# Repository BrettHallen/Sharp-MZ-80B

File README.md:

# Sharp MZ-80B
My little repository of information about Sharp's MZ-80B all-in-one business computer from 1981.<br>

The MZ-80B is an evolution of the MZ-80K.<br>

WORK IN PROGRESS.<br>

NOTE! Any PCB designs are untested unless stated otherwise.  I have done my best to recreate them based on the schematics in the Service Manual.  (15/Feb/2026)<br>

## Videos
- [Part 1: Initial look & disassembly](https://youtu.be/cHQdRs1u79s)
- [Part 2: Keyboard refurbishment starts](https://youtu.be/vS2Di7rVlAI)
- [Part 3: Power Supply](/https://youtu.be/JZkt_DzX6Ko)
- [Part 4: Monitor & Tape Deck](https://youtu.be/Ke3hOiWCVKM)

## Specs
- Z80 at 4MHz (LH0080A)
- Power: ±5V, +12V
- 32KB RAM, expandable to 64KB
- 2KB ROM (Initial Program Loader, IPL)
- 2KB Character Generator ROM
- 2KB Character RAM
- 8KB Graphics RAM, expandable to 16KB (MZ-80GMK)

## [Components](/Components)
- IC2: Sharp X0240PA (Gate Array 14297)
- IC3: Sharp LH0080A (Z80 CPU)
- IC8: Sharp IX0285PA (IPL Boot ROM, 334-5700)
- IC19: 8253 PIT (Progammable Interval Timer)
- IC23: NEC D8255AC-5 PPI (Programmable Peripheral Interface)
- IC24: Sharp LH0081A (Z80 PIO)
- IC41: Toshiba TMM2016P-1 (2KB S-RAM)
- IC42: Sharp X0241PA (Gate Array 14298)
- IC43: Sharp X0242PA (Gate Array 14299)
- IC44: Sharp IX0286PA (CG-ROM, 334P-5701)
- DRAM: Sharp LH4116-3 (16k x 1-bit)

## [Manuals](/Manuals)
- MZ-80B Service Manual
- MZ-80B Owners Manual

## [ROMs](/ROMs)
- 2KB Initial Program Loader (IPL)
- 2KB Character Generator

## [32KB RAM Expansion](/Sharp_MZ-80B_RAM_III_IV_Expansion)
Internal expansion board to increase the RAM from 32KB to 64KB.  This design is from the Service Manual and so currently uses 4116 RAM chips.<br>

## [Base 8KB Graphics RAM (MZ-80GM)](/Sharp_MZ-80GM)
Reproduction of the base graphics RAM card (a.k.a. "GRAPHYICS-1") in the Sharp MZ-80B based on the service manual schematics.  I've updated it by replacing the original four 2KB 2016 SRAM chips with a single 32KB 62256.  Overkill, yes, but the 62256 is still available new - it reduces the chip count by four.<br>

## [8KB Graphics RAM Expansion (MZ-80GMK)](/Sharp_MZ-80GMK)
Expansion board (a.k.a. "GRAPHYICS-2") that connects to the internal Expansion Port (MZ-80EU) that doubles the graphics video RAM from 8KB to 16KB.  This design is from the Service Manual but uses a 32KB 62256 as these are still available new, rather than an obsolete 8KB 6264 or four 2KB 2016.<br>

## [DRAM to SRAM](/Sharp_MZ-80B_DRAM-to-SRAM)
Idea to replace the 16 x 4116 DRAMs of the original 32KB RAM plus the additional 16 x 4116 DRAMs of the expansion RAM with two 62256 SRAMs.<br>

## [Keyboard](/Keyboard)
Schematic and replacement PCB design.<br>

## [SD Card Interface](https://github.com/yanataka60/MZ-2000_SD)
Design (not mine!) to add SD card interface for the MZ-80B (and others).  It will work in an 80B with or without the Expansion Unit installed, which is neat.

## [Combo Graphics RAM + SD Interface](/Sharp_MZ-80GMSD)
As my MZ-80B doesn't have an expansion unit I thought about trying to add the 8KB Graphics RAM expansion (MZ-80GMK) aka "GRAPHYCS-2" on the same board as the SD interface above.  The SD board itself is still external, but the connection to the MZ-80B motherboard is included with the graphics RAM expansion.

## Power 
My 80B came from Japan so expects 100VAC and not the 240VAC we use in Australia.

### DC Requirements
| Voltage          | Current | Use                                |
|------------------|---------|------------------------------------|
| +5V regulated    | 2.5A    | motherboard & tape deck            |
| -5V regulated    | 10mA    | DRAM                               |
| +12V regulated   | 1.25A   | monitor & tape deck                |
| +12V unregulated |         | 9.5V-16.5V for tape deck solenoids |

### Connectors
Thanks to [Brad](https://www.youtube.com/@zbradbell) for figuring out they are TJC1-type.<br>

| Sharp ID      | TJC Type     | Use                                         |
|---------------|--------------|---------------------------------------------|
| QPLGN0303CEZZ | TJC1-3A      | 3-pin terminal for tape deck power on PSU   |
| DSOCN0083PAZZ | TJC1-3Y      | 3-pin socket & wires from tape deck to PSU  |
| QPLGN0103CEZZ | TJC1-1A      | 1-pin terminal for monitor power on PSU     |
| DSOCN0083PAZZ | TJC1-1Y      | 1-pin socket & wire from monitor to PSU     |
| DSOCN0098PAZZ | TJC1-4Y      | 4-pin socket & wire from PSU to motherboard |
| QPLGN0403CEZZ | TJC1-4A      | 4-pin terminal on motherboard               |
| QPLGN0303CEZZ | TJC1-3A      | 3-pin terminal for Expansion Unit power     |
|               | TJC1-T       | Contact type for sockets                    |

- [QPLGN0303CEZZ](/Images/Sharp_MZ-80B_QPLGN0303CEZZ_1.jpg)
- [DSOCN0098PAZZ](/Images/Sharp_MZ-80B_DSOCN0098PAZZ_1.png)

### New DC Power Supply
To solve my 240VAC-to-100VAC problem I thought about using a DC power supply input and then lazily using modern DC-DC switching regulators.  The main issue I can see is that the original design uses an unregulated +12VDC to power the tape eject solenoid.  This is picked up from the rectified transformer output before the +12VDC regulator which powers the monitor & tape.<br>

The tape solenoid expects a voltage between 9.5V and 16.5V.<br>

My idea was to, ahem, simply use a +15VDC input for the solenoid, and then use separate +5V, -5V and +12V regulators for the regulated supplies.  I've added some capacitors to try to soak up any voltage spikes generated by the solenoid action.<br>

Some notes:
- If I can replace the DRAM with SRAM, there is no longer a need for the -5V rail
- If I don't physically use the tape deck then there is no need for the +15V, i.e. "unregulated +12V"

## [External Audio/Video Output](/Sharp_MZ-CVBS)
A re-design of an [existing design](https://github.com/gamo256/MZ_CVBS) for replacing the CRT with an LCD, I think.  The original design uses obsolete parts (well, hard to get in Australia) so I've tried to re-design.  Let's see if it works ...<br>

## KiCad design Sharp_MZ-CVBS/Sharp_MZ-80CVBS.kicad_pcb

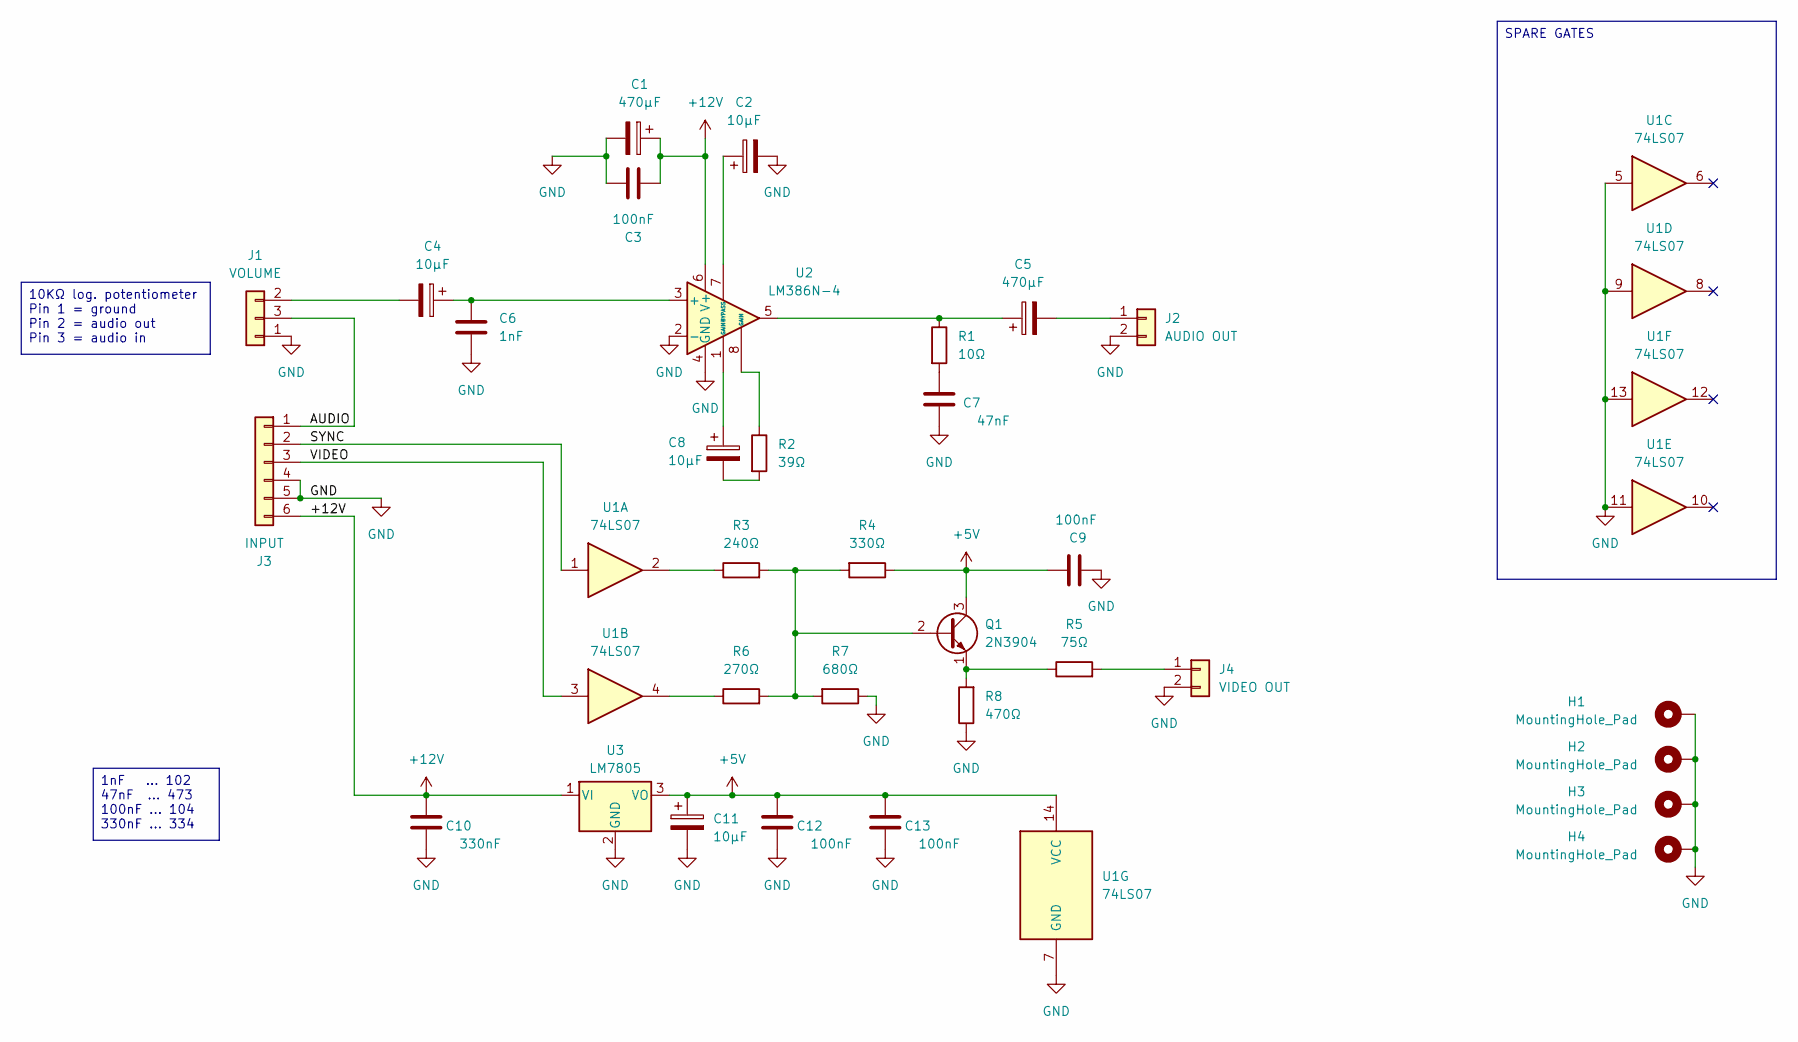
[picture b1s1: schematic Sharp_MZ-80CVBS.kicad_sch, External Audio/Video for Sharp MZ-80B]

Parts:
C1, C5: 470µF; CP_Radial_D10.0mm_P5.00mm
C2, C4, C8, C11: 10µF; CP_Radial_D5.0mm_P2.50mm
C3, C9, C12, C13: 100nF; C_Disc_D3.8mm_W2.6mm_P2.50mm
C6: 1nF; C_Disc_D3.8mm_W2.6mm_P2.50mm
C7: 47nF; C_Disc_D3.8mm_W2.6mm_P2.50mm
C10: 330nF; C_Disc_D3.8mm_W2.6mm_P2.50mm
H1, H2, H3, H4: MountingHole_Pad; MountingHole_3.2mm_M3_Pad
J1: VOLUME; PinHeader_1x03_P2.54mm_Vertical
J2: AUDIO OUT; PinHeader_1x02_P2.54mm_Vertical
J3: INPUT; PinHeader_1x06_P2.54mm_Vertical
J4: VIDEO OUT; PinHeader_1x02_P2.54mm_Vertical
Q1: 2N3904; TO-92_HandSolder
R1: 10Ω; R_Axial_DIN0207_L6.3mm_D2.5mm_P7.62mm_Horizontal
R2: 39Ω; R_Axial_DIN0207_L6.3mm_D2.5mm_P7.62mm_Horizontal
R3: 240Ω; R_Axial_DIN0207_L6.3mm_D2.5mm_P7.62mm_Horizontal
R4: 330Ω; R_Axial_DIN0207_L6.3mm_D2.5mm_P7.62mm_Horizontal
R5: 75Ω; R_Axial_DIN0207_L6.3mm_D2.5mm_P7.62mm_Horizontal
R6: 270Ω; R_Axial_DIN0207_L6.3mm_D2.5mm_P7.62mm_Horizontal
R7: 680Ω; R_Axial_DIN0207_L6.3mm_D2.5mm_P7.62mm_Horizontal
R8: 470Ω; R_Axial_DIN0207_L6.3mm_D2.5mm_P7.62mm_Horizontal
U1: 74LS07; DIP-14_W7.62mm
U2: LM386N-4; DIP-8_W7.62mm
U3: LM7805; TO-220-3_Horizontal_TabDown

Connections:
+5V: C9.1, C11.1, C12.1, C13.1, Q1.3 (C), R4.1, U1.14 (VCC), U3.3 (VO)
+12V: C1.1, C3.1, C10.1, J3.6, U2.6 (V+), U3.1 (VI)
/AUDIO: J1.3, J3.1
/SYNC: J3.2, U1.1
/VIDEO: J3.3, U1.3
GND: C1.2, C2.2, C3.2, C6.2, C7.2, C9.2, C10.2, C11.2, C12.2, C13.2, H1.1 (1_1), H2.1 (1_1), H3.1 (1_1), H4.1 (1_1), J1.1, J2.2, J3.4, J3.5, J4.2, R7.1, R8.1, U1.5, U1.7 (GND), U1.9, U1.11, U1.13, U2.2 (-), U2.4 (GND), U3.2 (GND)
unnamed: C5.1, R1.1, U2.5
unnamed: C7.1, R1.2
unnamed: C8.1, U2.1 (GAIN)
unnamed: C8.2, R2.2
unnamed: C4.2, J1.2
unnamed: C5.2, J2.1
unnamed: J4.1, R5.2
unnamed: Q1.2 (B), R3.2, R4.2, R6.2, R7.2
unnamed: Q1.1 (E), R5.1, R8.2
unnamed: R2.1, U2.8 (GAIN)
unnamed: R3.1, U1.2
unnamed: R6.1, U1.4
unnamed: C4.1, C6.1, U2.3 (+)
unnamed: C2.1, U2.7 (BYPASS)

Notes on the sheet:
1nF ... 102 47nF ... 473 100nF ... 104 330nF ... 334
SPARE GATES
10KΩ log. potentiometer Pin 1 = ground Pin 2 = audio out Pin 3 = audio in

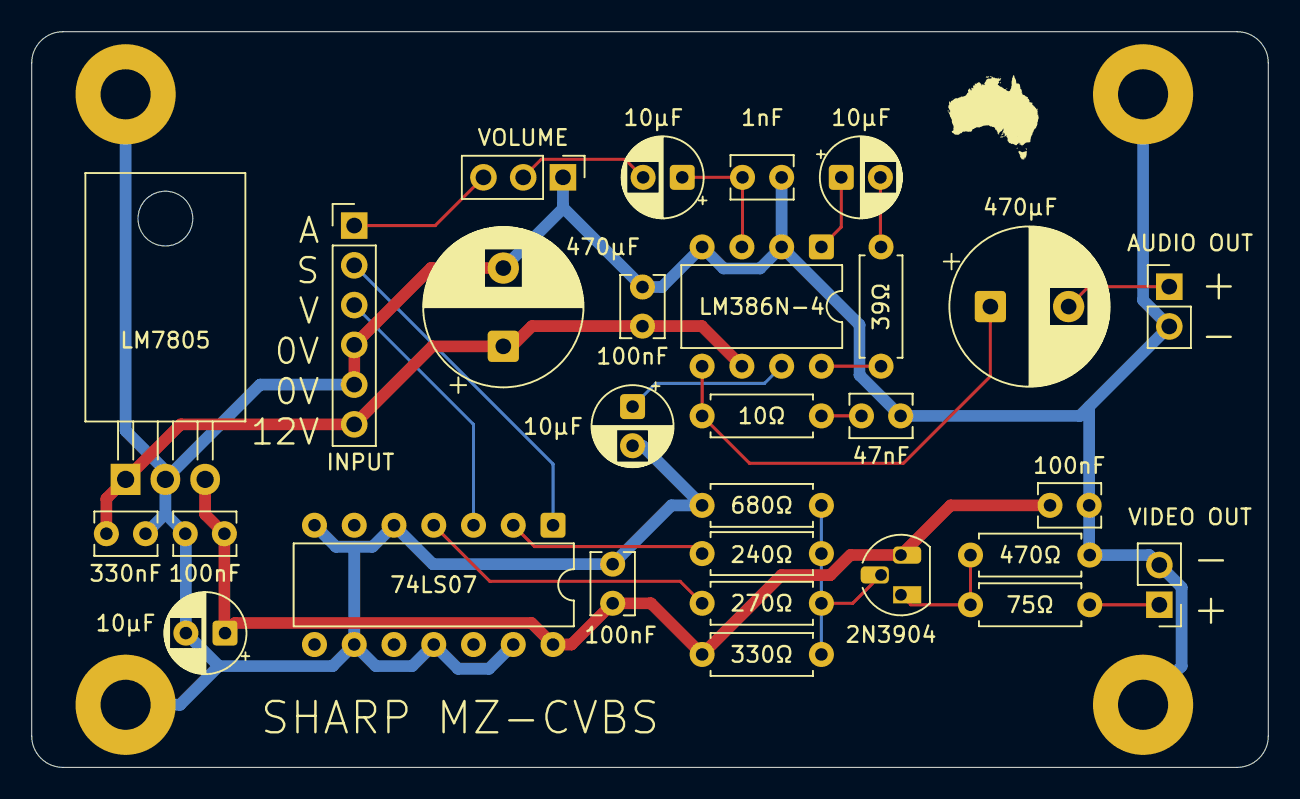
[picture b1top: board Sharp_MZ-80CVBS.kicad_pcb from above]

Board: 2 copper layers, 79.0 x 47.0 mm, 33 parts (0 on the bottom side), 20 nets.

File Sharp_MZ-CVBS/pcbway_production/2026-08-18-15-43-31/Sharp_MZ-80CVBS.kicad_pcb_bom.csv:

Designator,Quantity,Value,Footprint,Package,MPN,DNP,Mount_Type,Description,KiLib_Generator,Sim.Device,Sim.Pins
"C1, C5",2,470µF,CP_Radial_D10.0mm_P5.00mm,,,,tht,Polarized capacitor,capacitor/THT/other,,
C10,1,330nF,C_Disc_D3.8mm_W2.6mm_P2.50mm,,,,tht,Unpolarized capacitor,capacitor/THT/other,,
"C11, C2, C4, C8",4,10µF,CP_Radial_D5.0mm_P2.50mm,,,,tht,Polarized capacitor,capacitor/THT/other,,
"C12, C13, C3, C9",4,100nF,C_Disc_D3.8mm_W2.6mm_P2.50mm,,,,tht,Unpolarized capacitor,capacitor/THT/other,,
C6,1,1nF,C_Disc_D3.8mm_W2.6mm_P2.50mm,,,,tht,Unpolarized capacitor,capacitor/THT/other,,
C7,1,47nF,C_Disc_D3.8mm_W2.6mm_P2.50mm,,,,tht,Unpolarized capacitor,capacitor/THT/other,,
J1,1,VOLUME,PinHeader_1x03_P2.54mm_Vertical,,,,tht,"Generic connector, single row, 01x03, script generated (kicad-library-utils/schlib/autogen/connector/)",connector/pin_header_socket,,
J2,1,AUDIO OUT,PinHeader_1x02_P2.54mm_Vertical,,,,tht,"Generic connector, single row, 01x02, script generated (kicad-library-utils/schlib/autogen/connector/)",connector/pin_header_socket,,
J3,1,INPUT,PinHeader_1x06_P2.54mm_Vertical,,,,tht,"Generic connector, single row, 01x06, script generated (kicad-library-utils/schlib/autogen/connector/)",connector/pin_header_socket,,
J4,1,VIDEO OUT,PinHeader_1x02_P2.54mm_Vertical,,,,tht,"Generic connector, single row, 01x02, script generated (kicad-library-utils/schlib/autogen/connector/)",connector/pin_header_socket,,
Q1,1,2N3904,TO-92_HandSolder,,,,tht,"0.2A Ic, 40V Vce, Small Signal NPN Transistor, TO-92",,NPN,1=E 2=B 3=C
R1,1,10Ω,R_Axial_DIN0207_L6.3mm_D2.5mm_P7.62mm_Horizontal,,,,tht,Resistor,resistor/THT,,
R2,1,39Ω,R_Axial_DIN0207_L6.3mm_D2.5mm_P7.62mm_Horizontal,,,,tht,Resistor,resistor/THT,,
R3,1,240Ω,R_Axial_DIN0207_L6.3mm_D2.5mm_P7.62mm_Horizontal,,,,tht,Resistor,resistor/THT,,
R4,1,330Ω,R_Axial_DIN0207_L6.3mm_D2.5mm_P7.62mm_Horizontal,,,,tht,Resistor,resistor/THT,,
R5,1,75Ω,R_Axial_DIN0207_L6.3mm_D2.5mm_P7.62mm_Horizontal,,,,tht,Resistor,resistor/THT,,
R6,1,270Ω,R_Axial_DIN0207_L6.3mm_D2.5mm_P7.62mm_Horizontal,,,,tht,Resistor,resistor/THT,,
R7,1,680Ω,R_Axial_DIN0207_L6.3mm_D2.5mm_P7.62mm_Horizontal,,,,tht,Resistor,resistor/THT,,
R8,1,470Ω,R_Axial_DIN0207_L6.3mm_D2.5mm_P7.62mm_Horizontal,,,,tht,Resistor,resistor/THT,,
U1,1,74LS07,DIP-14_W7.62mm,,,,tht,Hex Buffers and Drivers With Open Collector High Voltage Outputs,package/DIP/legacy,,
U2,1,LM386N-4,DIP-8_W7.62mm,,,,tht,"Low Voltage Audio Power Amplifier, DIP-8/SOIC-8/SSOP-8",package/DIP/legacy,,
U3,1,LM7805,TO-220-3_Horizontal_TabDown,,,,tht,"Positive 1A 35V Linear Regulator, Fixed Output 5V, TO-220",package/TO_SOT/THT,,

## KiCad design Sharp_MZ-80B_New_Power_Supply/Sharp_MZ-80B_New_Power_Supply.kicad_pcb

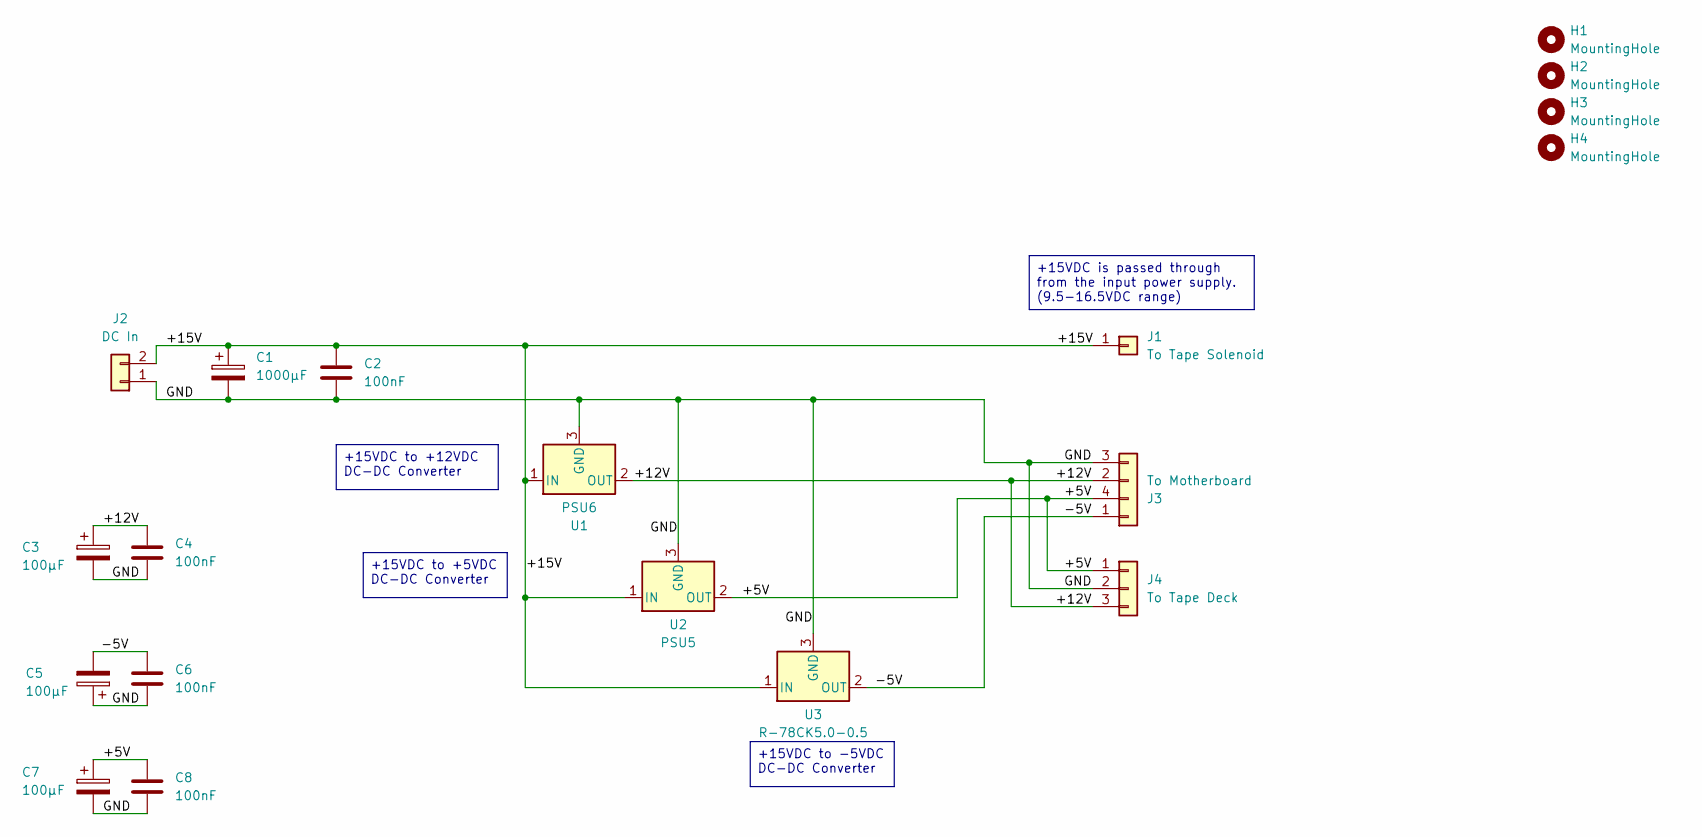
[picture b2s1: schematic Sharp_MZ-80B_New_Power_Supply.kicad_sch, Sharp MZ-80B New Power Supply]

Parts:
C1: 1000µF; CP_Radial_D16.0mm_P7.50mm
C2, C4, C6, C8: 100nF; C_Disc_D3.8mm_W2.6mm_P2.50mm
C3, C5, C7: 100µF; CP_Radial_D7.5mm_P2.50mm
H1, H2, H3, H4: MountingHole; MountingHole_3.2mm_M3
J1: To Tape Solenoid; TJC1-1A
J2: DC In; TJC1-2A
J3: To Motherboard; TJC1-4A
J4: To Tape Deck; TJC1-3A
U1: PSU6; TO-3
U2: PSU5; TO-3
U3: R-78CK5.0-0.5; TO-220-3_Vertical

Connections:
/+5V: C7.1, C8.1, J3.4, J4.1, U2.2 (OUT)
/+12V: C3.1, C4.1, J3.2, J4.3, U1.2 (OUT)
/+15V: C1.1, C2.1, J1.1, J2.2, U1.1 (IN), U2.1 (IN), U3.1 (IN)
/-5V: C5.2, C6.1, J3.1, U3.2 (OUT)
/GND: C1.2, C2.2, C3.2, C4.2, C5.1, C6.2, C7.2, C8.2, J2.1, J3.3, J4.2, U1.3 (GND), U2.3 (GND), U3.3 (GND)

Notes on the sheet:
+15VDC to +5VDC DC-DC Converter
+15VDC is passed through from the input power supply. (9.5-16.5VDC range)
+15VDC to +12VDC DC-DC Converter
+15VDC to -5VDC DC-DC Converter

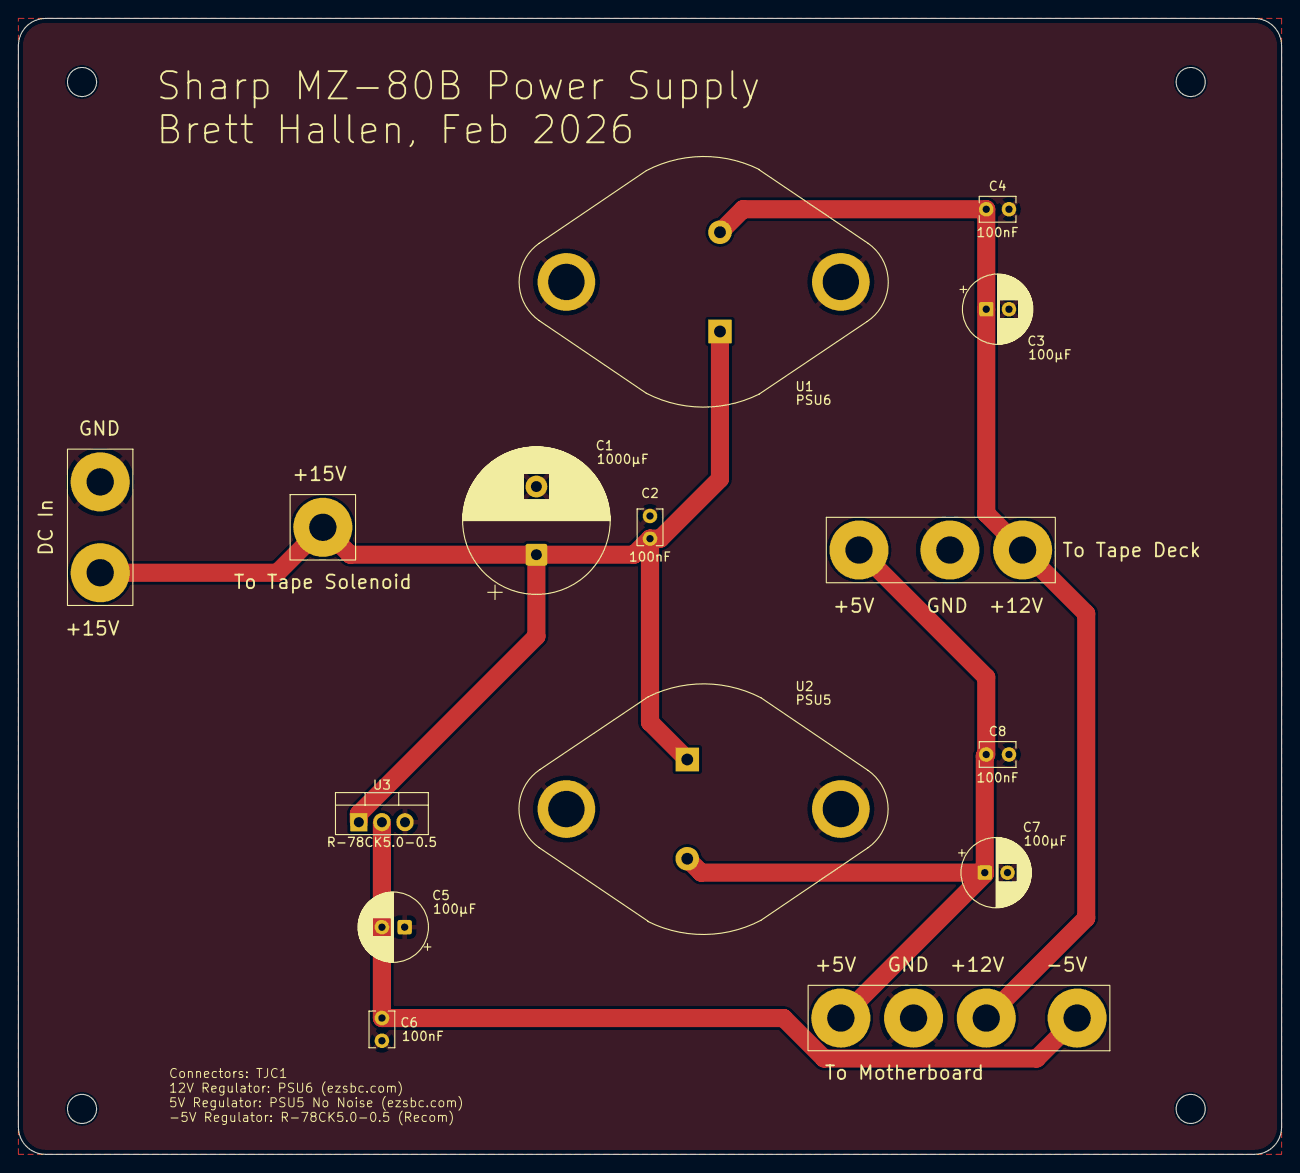
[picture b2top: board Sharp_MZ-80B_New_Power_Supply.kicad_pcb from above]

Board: 2 copper layers, 139.0 x 125.0 mm, 19 parts (0 on the bottom side), 5 nets.

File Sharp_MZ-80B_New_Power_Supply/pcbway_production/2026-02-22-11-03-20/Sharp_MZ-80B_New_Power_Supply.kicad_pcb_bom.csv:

Designator,Quantity,Value,Footprint,Package,MPN,DNP,Mount_Type,Description
C1,1,1000µF,CP_Radial_D16.0mm_P7.50mm,,,,tht,Polarized capacitor
"C2, C4, C6, C8",4,100nF,C_Disc_D3.8mm_W2.6mm_P2.50mm,,,,tht,Unpolarized capacitor
"C3, C5, C7",3,100µF,CP_Radial_D7.5mm_P2.50mm,,,,tht,Polarized capacitor
J1,1,To Tape Solenoid,TJC1-1A,,,,tht,"Generic connector, single row, 01x01, script generated (kicad-library-utils/schlib/autogen/connector/)"
J2,1,DC In,TJC1-2A,,,,tht,"Generic connector, single row, 01x02, script generated (kicad-library-utils/schlib/autogen/connector/)"
J3,1,To Motherboard,TJC1-4A,,,,tht,"Generic connector, single row, 01x04, script generated (kicad-library-utils/schlib/autogen/connector/)"
J4,1,To Tape Deck,TJC1-3A,,,,tht,"Generic connector, single row, 01x03, script generated (kicad-library-utils/schlib/autogen/connector/)"
U1,1,PSU6,TO-3,,,,tht,"Positive 1.5A 35V Linear Regulator, Fixed Output 5V, TO-220/TO-263/TO-252"
U2,1,PSU5,TO-3,,,,tht,"Positive 1.5A 35V Linear Regulator, Fixed Output 5V, TO-220/TO-263/TO-252"
U3,1,R-78CK5.0-0.5,TO-220-3_Vertical,,,,tht,"Positive 1.5A 35V Linear Regulator, Fixed Output 5V, TO-220/TO-263/TO-252"

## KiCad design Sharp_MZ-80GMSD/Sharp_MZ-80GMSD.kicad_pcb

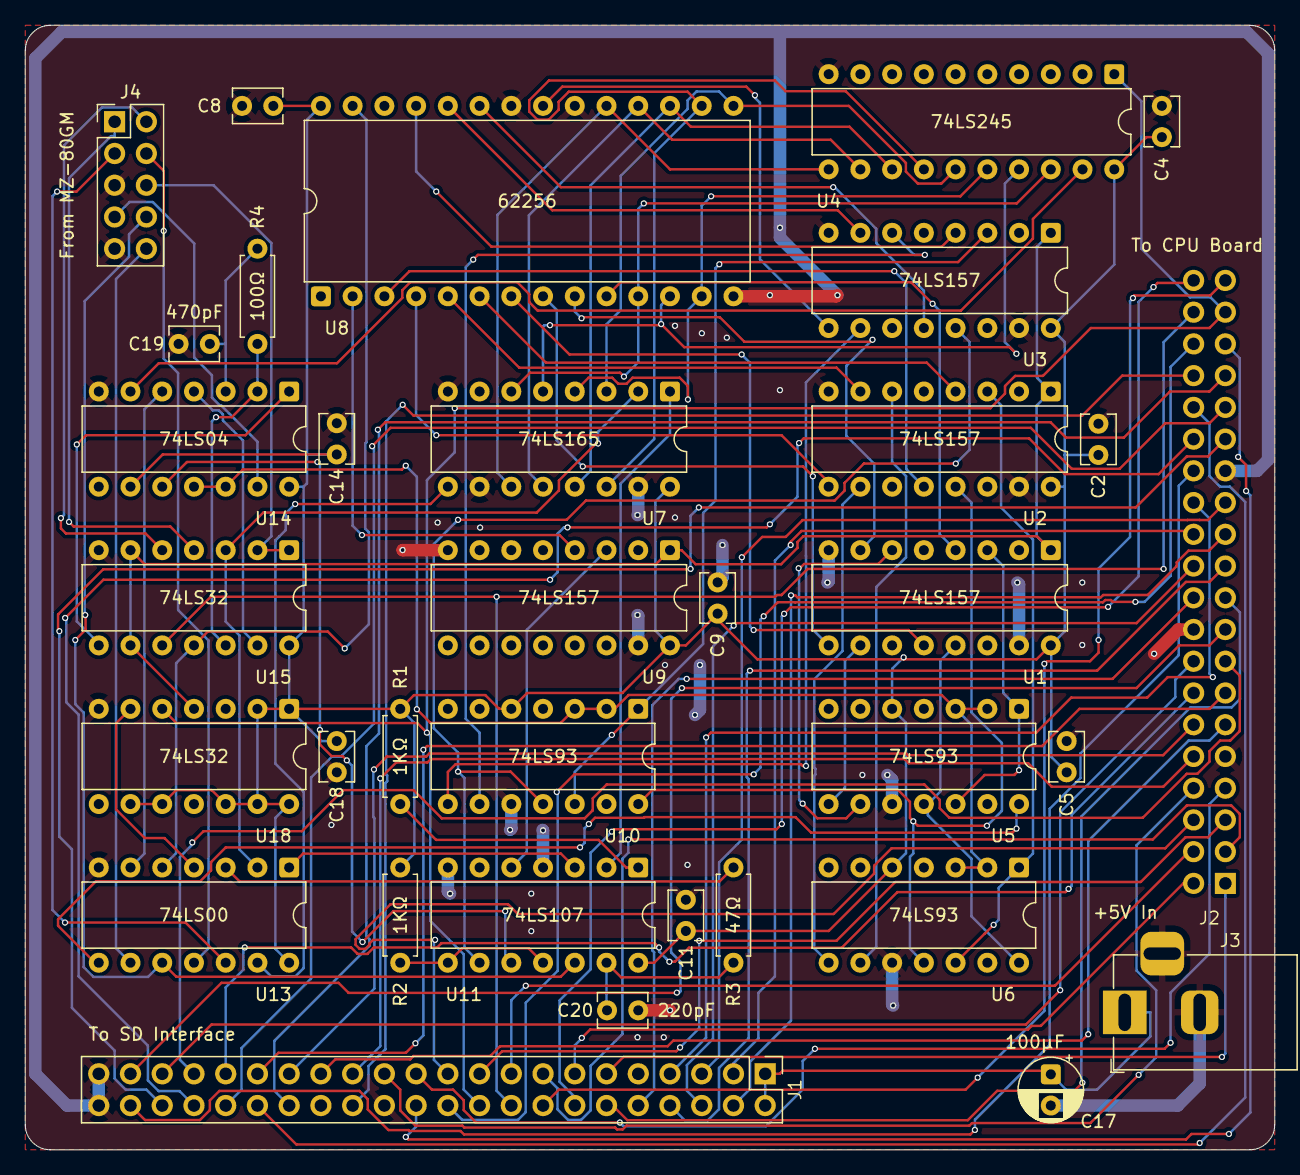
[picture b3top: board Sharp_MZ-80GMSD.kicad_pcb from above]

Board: 2 copper layers, 100.0 x 90.0 mm, 34 parts (1 on the bottom side), 102 nets.

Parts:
C2, C4, C5, C8, C9, C11, C14, C18: 100nF; C_Disc_D3.8mm_W2.6mm_P2.50mm
C17: 100µF; CP_Radial_D5.0mm_P2.50mm
C19: 470pF; C_Disc_D3.8mm_W2.6mm_P2.50mm
C20: 220pF; C_Disc_D3.8mm_W2.6mm_P2.50mm
J1: To SD Interface; PinHeader_2x22_P2.54mm_Vertical
J2: To CPU Board; PinSocket_2x20_P2.54mm_Vertical
J3: +5V In; BarrelJack_Horizontal
J4: From MZ-80GM; PinHeader_2x05_P2.54mm_Vertical
R1, R2: 1KΩ; R_Axial_DIN0207_L6.3mm_D2.5mm_P7.62mm_Horizontal
R3: 47Ω; R_Axial_DIN0207_L6.3mm_D2.5mm_P7.62mm_Horizontal
R4: 100Ω; R_Axial_DIN0207_L6.3mm_D2.5mm_P7.62mm_Horizontal
U1, U2, U3, U9: 74LS157; DIP-16_W7.62mm
U4: 74LS245; DIP-20_W7.62mm
U5, U6, U10: 74LS93; DIP-14_W7.62mm
U7: 74LS165; DIP-16_W7.62mm
U8: 62256; DIP-28_W15.24mm
U11: 74LS107; DIP-14_W7.62mm
U13: 74LS00; DIP-14_W7.62mm
U14: 74LS04; DIP-14_W7.62mm
U15, U18: 74LS32; DIP-14_W7.62mm

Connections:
+5V: C17.1, J1.A1 (Pin_a1), J1.B1 (Pin_b1), J3.1
/1M: J4.8, U11.12 (C), U13.10
/8M: J4.6, U15.1, U15.2
/A0: J1.A21 (Pin_a21), J2.17
/A1: J1.A20 (Pin_a20), J2.16
/A2: J1.A19 (Pin_a19), J2.15
/A3: J1.A18 (Pin_a18), J2.14
/A4: J1.A17 (Pin_a17), J2.13
/A5: J1.A16 (Pin_a16), J2.12
/A6: J1.A15 (Pin_a15), J2.11
/A7: J1.A14 (Pin_a14), J2.10
/A8: J1.A13 (Pin_a13), J2.8
/A9: J1.A12 (Pin_a12), J2.7
/A10: J1.A11 (Pin_a11), J2.6
/A11: J1.A10 (Pin_a10), J2.5
/A12: J1.A9 (Pin_a9), J2.4
/A13: J1.A8 (Pin_a8), J2.3
/A14: J1.A7 (Pin_a7), J2.2
/A15: J1.A6 (Pin_a6), J2.1
/BUS Φ: J1.B7 (Pin_b7), J2.40
/CLOCK: U7.2 (CP), U13.2, U15.3
/D0: J1.A4 (Pin_a4), J2.26
/D1: J1.A3 (Pin_a3), J2.25
/D2: J1.A2 (Pin_a2), J2.24
/D3: J1.B2 (Pin_b2), J2.23
/D4: J1.B3 (Pin_b3), J2.22
/D5: J1.B4 (Pin_b4), J2.21
/D6: J1.B5 (Pin_b5), J2.20
/D7: J1.B6 (Pin_b6), J2.19
/G0: J4.3, U13.12
/G1: J4.1, U15.4
/G_{0}: U1.3 (I1a), U5.1 (CP1..3), U5.12 (Q0)
/G_{1}: U1.6 (I1b), U5.9 (Q1)
/G_{2}: U1.10 (I1c), U5.8 (Q2)
/G_{3}: U1.13 (I1d), U5.11 (Q3), U6.14 (CP0)
/G_{4}: U2.3 (I1a), U6.1 (CP1..3), U6.12 (Q0)
/G_{5}: U2.6 (I1b), U6.9 (Q1)
/G_{6}: U2.10 (I1c), U6.8 (Q2)
/G_{7}: U2.13 (I1d), U6.11 (Q3), U10.14 (CP0)
/G_{8}: U3.3 (I1a), U10.1 (CP1..3), U10.12 (Q0)
/G_{9}: U3.6 (I1b), U10.9 (Q1)
/G_{10}: U3.10 (I1c), U10.8 (Q2)
/G_{11}: U3.13 (I1d), U10.11 (Q3), U11.9 (C)
/G_{12}: U9.3 (I1a), U11.5 (Q)
/IE0: J1.B16 (Pin_b16), J2.33
/RA_{0}: U1.4 (Za), U8.10 (A0)
/RA_{1}: U1.7 (Zb), U8.9 (A1)
/RA_{2}: U1.9 (Zc), U8.8 (A2)
/RA_{3}: U1.12 (Zd), U8.7 (A3)
/RA_{4}: U2.4 (Za), U8.6 (A4)
/RA_{5}: U2.7 (Zb), U8.5 (A5)
/RA_{6}: U2.9 (Zc), U8.4 (A6)
/RA_{7}: U2.12 (Zd), U8.3 (A7)
/RA_{8}: U3.4 (Za), U8.25 (A8)
/RA_{9}: U3.7 (Zb), U8.24 (A9)
/RA_{10}: U3.9 (Zc), U8.21 (A10)
/RA_{11}: U3.12 (Zd), U8.23 (A11)
/RA_{12}: U8.2 (A12), U9.4 (Za)
/RD_{0}: U4.18 (B0), U7.6 (D7), U8.11 (Q0)
/RD_{1}: U4.17 (B1), U7.5 (D6), U8.12 (Q1)
/RD_{2}: U4.16 (B2), U7.4 (D5), U8.13 (Q2)
/RD_{3}: U4.15 (B3), U7.3 (D4), U8.15 (Q3)
/RD_{4}: U4.14 (B4), U7.14 (D3), U8.16 (Q4)
/RD_{5}: U4.13 (B5), U7.13 (D2), U8.17 (Q5)
/RD_{6}: U4.12 (B6), U7.12 (D1), U8.18 (Q6)
/RD_{7}: U4.11 (B7), U7.11 (D0), U8.19 (Q7)
/RESET: J1.B17 (Pin_b17), J2.32
/SELECT: U1.1 (S), U2.1 (S), U3.1 (S), U9.1 (S), U15.6, U15.9, U18.4
/SHIFT/~LOAD: U7.1 (~PL), U11.2 (~Q)
/~C SED: J4.2, U15.5
/~EX INT: J1.B19 (Pin_b19), J2.30
/~EX RESET: J1.B18 (Pin_b18), J2.31
/~EX WAIT: J1.B20 (Pin_b20), J2.29
/~G OUT 2: J4.4, U13.11
/~HALT: J1.B14 (Pin_b14), J2.34
/~HBLK: J4.10, U13.9
/~IOREQ: J1.B11 (Pin_b11), J2.36
/~M1: J1.B8 (Pin_b8), J2.39
/~MNI: J1.B21 (Pin_b21), J2.28
/~MREQ: J1.B12 (Pin_b12), J2.35
/~RD: J1.B10 (Pin_b10), J2.37, U4.1 (A->B), U18.5
/~VBLK: J4.7, U14.13
/~WE: U8.27 (~WE), U13.5, U15.11
/~WR: J1.B9 (Pin_b9), J2.38, U15.10
GND: C2.2, C4.2, C5.2, C8.2, C9.1, C11.1, C14.1, C17.2, C18.1, C19.1, C20.2, J1.A5 (Pin_a5), J1.A22 (Pin_a22), J1.B13 (Pin_b13), J1.B22 (Pin_b22), J2.9, J2.18, J2.27, J3.2, J4.5, J4.9, U1.8 (GND), U1.15 (E), U2.8 (GND), U2.15 (E), U3.8 (GND), U3.15 (E), U4.10 (GND), U5.10 (GND), U6.10 (GND), U7.8 (GND), U7.10 (DS), U7.15 (~CE), U8.14 (GND), U8.20 (~CS), U8.22 (~OE), U9.8 (GND), U9.15 (E), U10.10 (GND), U11.4 (K), U11.7 (GND), U13.7 (GND), U14.7 (GND), U15.7 (GND), U18.7 (GND)
unnamed: C19.2, R4.2, U14.3
unnamed: R3.2, U13.3
unnamed: R4.1, U14.2, U15.12
unnamed: U4.19 (CE), U14.6
unnamed: U5.14 (CP0), U13.8
unnamed: U7.9 (Q7), U13.13
unnamed: U5.2 (R0(1)), U5.3 (R0(2)), U6.2 (R0(1)), U6.3 (R0(2)), U10.2 (R0(1)), U10.3 (R0(2)), U14.11, U14.12
unnamed: R1.2, U11.1 (J)
unnamed: U11.3 (Q), U13.1
unnamed: C20.1, R3.1, U11.13 (~R)
unnamed: R2.2, U11.8 (J), U11.11 (K)
unnamed: U11.10 (~R), U14.10
unnamed: U13.4, U18.6
unnamed: U13.6, U14.5
unnamed: U14.1, U15.8
unnamed: U14.4, U15.13
VCC: C2.1, C4.1, C5.1, C8.1, C9.2, C11.2, C14.2, C18.2, R1.1, R2.1, U1.16 (VCC), U2.16 (VCC), U3.16 (VCC), U4.20 (VCC), U5.5 (VCC), U6.5 (VCC), U7.16 (VCC), U8.28 (VCC), U9.16 (VCC), U10.5 (VCC), U11.14 (VCC), U13.14 (VCC), U14.9, U14.14 (VCC), U15.14 (VCC), U18.1, U18.2, U18.9, U18.10, U18.12, U18.13, U18.14 (VCC)

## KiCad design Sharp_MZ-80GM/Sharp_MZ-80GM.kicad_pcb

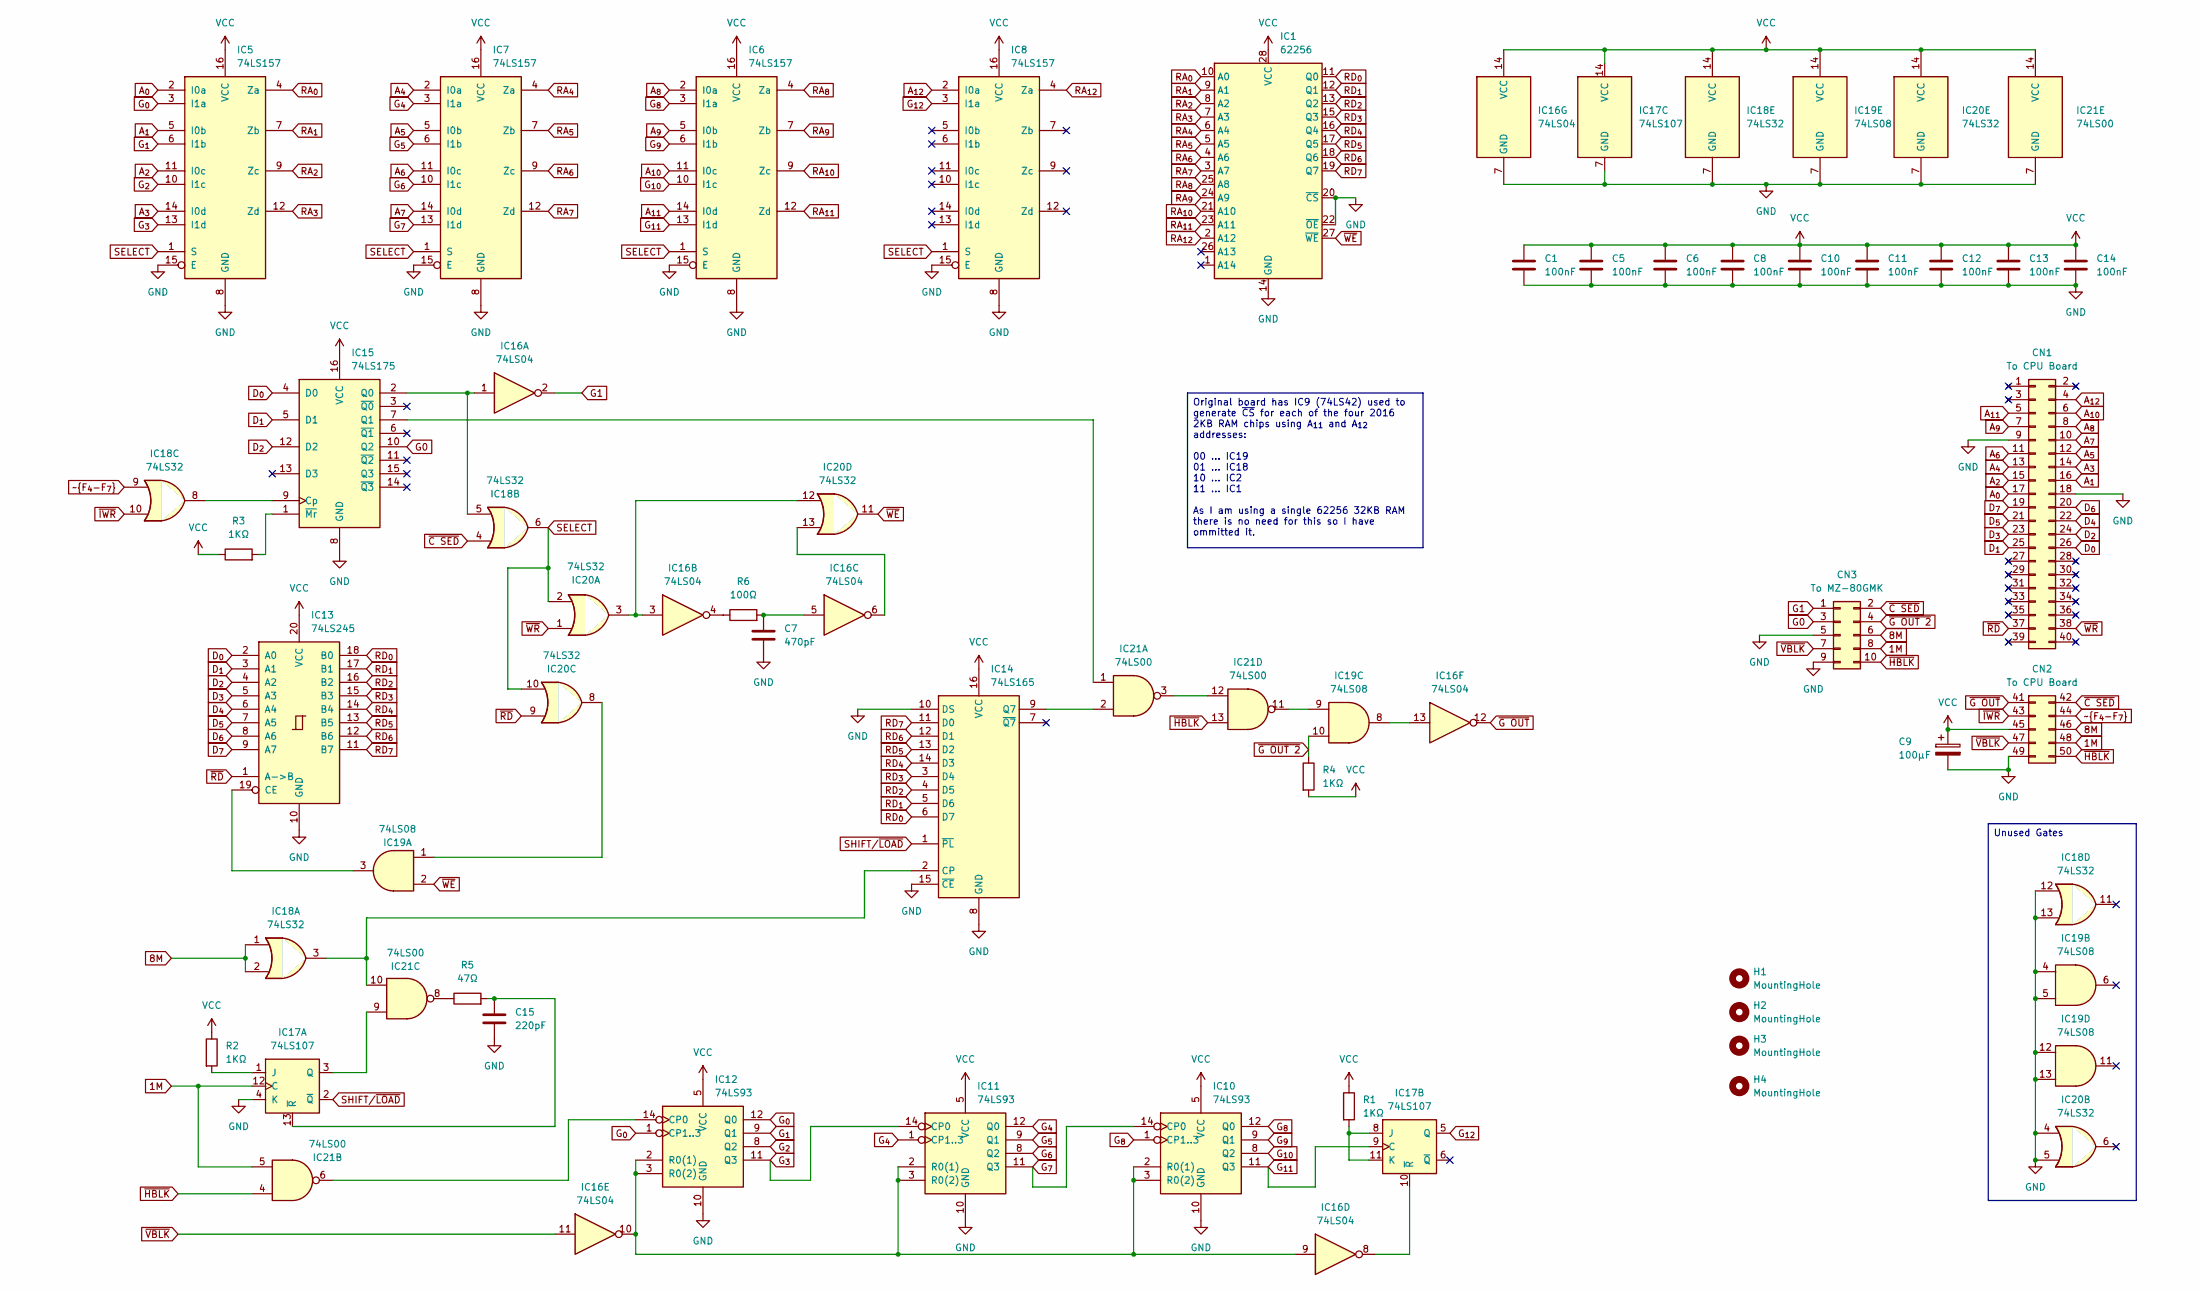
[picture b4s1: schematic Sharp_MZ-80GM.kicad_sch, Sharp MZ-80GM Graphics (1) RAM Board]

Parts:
C1, C5, C6, C8, C10, C11, C12, C13, C14: 100nF; C_Disc_D3.8mm_W2.6mm_P2.50mm
C7: 470pF; C_Disc_D3.8mm_W2.6mm_P2.50mm
C9: 100µF; CP_Radial_D5.0mm_P2.50mm
C15: 220pF; C_Disc_D3.8mm_W2.6mm_P2.50mm
CN1: To CPU Board; PinHeader_2x20_P2.54mm_Vertical
CN2: To CPU Board; PinHeader_2x05_P2.54mm_Vertical
CN3: To MZ-80GMK; PinHeader_2x05_P2.54mm_Horizontal
H1, H2, H3, H4: MountingHole; MountingHole_5.3mm_M5
IC1: 62256; DIP-28_W15.24mm
IC5, IC6, IC7, IC8: 74LS157; DIP-16_W7.62mm
IC10, IC11, IC12: 74LS93; DIP-14_W7.62mm
IC13: 74LS245; DIP-20_W7.62mm
IC14: 74LS165; DIP-16_W7.62mm
IC15: 74LS175; DIP-16_W7.62mm
IC16: 74LS04; DIP-14_W7.62mm
IC17: 74LS107; DIP-14_W7.62mm
IC18, IC20: 74LS32; DIP-14_W7.62mm
IC19: 74LS08; DIP-14_W7.62mm
IC21: 74LS00; DIP-14_W7.62mm
R1, R2, R3, R4: 1KΩ; R_Axial_DIN0207_L6.3mm_D2.5mm_P7.62mm_Horizontal
R5: 47Ω; R_Axial_DIN0207_L6.3mm_D2.5mm_P7.62mm_Horizontal
R6: 100Ω; R_Axial_DIN0207_L6.3mm_D2.5mm_P7.62mm_Horizontal

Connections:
1M: CN2.48 (Pin_8), CN3.8, IC17.12 (C), IC21.5
8M: CN2.46 (Pin_6), CN3.6, IC18.1, IC18.2
A_{0}: CN1.17 (A0), IC5.2 (I0a)
A_{1}: CN1.16 (A1), IC5.5 (I0b)
A_{2}: CN1.15 (A2), IC5.11 (I0c)
A_{3}: CN1.14 (A3), IC5.14 (I0d)
A_{4}: CN1.13 (A4), IC7.2 (I0a)
A_{5}: CN1.12 (A5), IC7.5 (I0b)
A_{6}: CN1.11 (A6), IC7.11 (I0c)
A_{7}: CN1.10 (A7), IC7.14 (I0d)
A_{8}: CN1.8 (A8), IC6.2 (I0a)
A_{9}: CN1.7 (A9), IC6.5 (I0b)
A_{10}: CN1.6 (A10), IC6.11 (I0c)
A_{11}: CN1.5 (A11), IC6.14 (I0d)
A_{12}: CN1.4 (A12), IC8.2 (I0a)
D_{0}: CN1.26 (D0), IC13.2 (A0), IC15.4 (D0)
D_{1}: CN1.25 (D1), IC13.3 (A1), IC15.5 (D1)
D_{2}: CN1.24 (D2), IC13.4 (A2), IC15.12 (D2)
D_{3}: CN1.23 (D3), IC13.5 (A3)
D_{4}: CN1.22 (D4), IC13.6 (A4)
D_{5}: CN1.21 (D5), IC13.7 (A5)
D_{6}: CN1.20 (D6), IC13.8 (A6)
D_{7}: CN1.19 (D7), IC13.9 (A7)
G0: CN3.3, IC15.10 (Q2)
G1: CN3.1, IC16.2
GND: C1.2, C5.2, C6.2, C7.2, C8.2, C9.2, C10.2, C11.2, C12.2, C13.2, C14.2, C15.2, CN1.9 (GND), CN1.18 (GND), CN2.49 (GND), CN3.5, CN3.9, IC1.14 (GND), IC1.20 (~CS), IC1.22 (~OE), IC5.8 (GND), IC5.15 (E), IC6.8 (GND), IC6.15 (E), IC7.8 (GND), IC7.15 (E), IC8.8 (GND), IC8.15 (E), IC10.10 (GND), IC11.10 (GND), IC12.10 (GND), IC13.10 (GND), IC14.8 (GND), IC14.10 (DS), IC14.15 (~CE), IC15.8 (GND), IC16.7 (GND), IC17.4 (K), IC17.7 (GND), IC18.7 (GND), IC18.12, IC18.13, IC19.4, IC19.5, IC19.7 (GND), IC19.12, IC19.13, IC20.4, IC20.5, IC20.7 (GND), IC21.7 (GND)
G_{0}: IC5.3 (I1a), IC12.1 (CP1..3), IC12.12 (Q0)
G_{1}: IC5.6 (I1b), IC12.9 (Q1)
G_{2}: IC5.10 (I1c), IC12.8 (Q2)
G_{3}: IC5.13 (I1d), IC11.14 (CP0), IC12.11 (Q3)
G_{4}: IC7.3 (I1a), IC11.1 (CP1..3), IC11.12 (Q0)
G_{5}: IC7.6 (I1b), IC11.9 (Q1)
G_{6}: IC7.10 (I1c), IC11.8 (Q2)
G_{7}: IC7.13 (I1d), IC10.14 (CP0), IC11.11 (Q3)
G_{8}: IC6.3 (I1a), IC10.1 (CP1..3), IC10.12 (Q0)
G_{9}: IC6.6 (I1b), IC10.9 (Q1)
G_{10}: IC6.10 (I1c), IC10.8 (Q2)
G_{11}: IC6.13 (I1d), IC10.11 (Q3), IC17.9 (C)
G_{12}: IC8.3 (I1a), IC17.5 (Q)
unnamed: C7.1, IC16.5, R6.2
unnamed: IC10.2 (R0(1)), IC10.3 (R0(2)), IC11.2 (R0(1)), IC11.3 (R0(2)), IC12.2 (R0(1)), IC12.3 (R0(2)), IC16.9, IC16.10
unnamed: IC12.14 (CP0), IC21.6
unnamed: IC13.19 (CE), IC19.3
unnamed: IC14.2 (CP), IC18.3, IC21.10
unnamed: IC14.9 (Q7), IC21.2
unnamed: IC15.9 (Cp), IC18.8
unnamed: IC15.2 (Q0), IC16.1, IC18.5
unnamed: IC15.7 (Q1), IC21.1
unnamed: IC15.1 (~Mr), R3.2
unnamed: IC16.3, IC20.3, IC20.12
unnamed: IC16.4, R6.1
unnamed: IC16.6, IC20.13
unnamed: IC16.13, IC19.8
unnamed: IC17.1 (J), R2.2
unnamed: IC17.3 (Q), IC21.9
unnamed: C15.1, IC17.13 (~R), R5.2
unnamed: IC17.8 (J), IC17.11 (K), R1.2
unnamed: IC16.8, IC17.10 (~R)
unnamed: IC19.1, IC20.8
unnamed: IC19.9, IC21.11
unnamed: IC21.8, R5.1
unnamed: IC21.3, IC21.12
RA_{0}: IC1.10 (A0), IC5.4 (Za)
RA_{1}: IC1.9 (A1), IC5.7 (Zb)
RA_{2}: IC1.8 (A2), IC5.9 (Zc)
RA_{3}: IC1.7 (A3), IC5.12 (Zd)
RA_{4}: IC1.6 (A4), IC7.4 (Za)
RA_{5}: IC1.5 (A5), IC7.7 (Zb)
RA_{6}: IC1.4 (A6), IC7.9 (Zc)
RA_{7}: IC1.3 (A7), IC7.12 (Zd)
RA_{8}: IC1.25 (A8), IC6.4 (Za)
RA_{9}: IC1.24 (A9), IC6.7 (Zb)
RA_{10}: IC1.21 (A10), IC6.9 (Zc)
RA_{11}: IC1.23 (A11), IC6.12 (Zd)
RA_{12}: IC1.2 (A12), IC8.4 (Za)
RD_{0}: IC1.11 (Q0), IC13.18 (B0), IC14.6 (D7)
RD_{1}: IC1.12 (Q1), IC13.17 (B1), IC14.5 (D6)
RD_{2}: IC1.13 (Q2), IC13.16 (B2), IC14.4 (D5)
RD_{3}: IC1.15 (Q3), IC13.15 (B3), IC14.3 (D4)
RD_{4}: IC1.16 (Q4), IC13.14 (B4), IC14.14 (D3)
RD_{5}: IC1.17 (Q5), IC13.13 (B5), IC14.13 (D2)
RD_{6}: IC1.18 (Q6), IC13.12 (B6), IC14.12 (D1)
RD_{7}: IC1.19 (Q7), IC13.11 (B7), IC14.11 (D0)
SELECT: IC5.1 (S), IC6.1 (S), IC7.1 (S), IC8.1 (S), IC18.6, IC20.2, IC20.10
SHIFT/~LOAD: IC14.1 (~PL), IC17.2 (~Q)
VCC: C1.1, C5.1, C6.1, C8.1, C9.1, C10.1, C11.1, C12.1, C13.1, C14.1, CN2.45 (+5V), IC1.28 (VCC), IC5.16 (VCC), IC6.16 (VCC), IC7.16 (VCC), IC8.16 (VCC), IC10.5 (VCC), IC11.5 (VCC), IC12.5 (VCC), IC13.20 (VCC), IC14.16 (VCC), IC15.16 (VCC), IC16.14 (VCC), IC17.14 (VCC), IC18.14 (VCC), IC19.14 (VCC), IC20.14 (VCC), IC21.14 (VCC), R1.1, R2.1, R3.1, R4.2
~C SED: CN2.42 (Pin_2), CN3.2, IC18.4
~F_{4-F_{7}}: CN2.44 (Pin_4), IC18.9
~G OUT 2: CN3.4, IC19.10, R4.1
~G OUT: CN2.41 (Pin_1), IC16.12
~HBLK: CN2.50 (Pin_10), CN3.10, IC21.4, IC21.13
~IWR: CN2.43 (Pin_3), IC18.10
~RD: CN1.37 (~RD), IC13.1 (A->B), IC20.9
~VBLK: CN2.47 (Pin_7), CN3.7, IC16.11
~WE: IC1.27 (~WE), IC19.2, IC20.11
~WR: CN1.38 (~WR), IC20.1

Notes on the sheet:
Original board has IC9 (74LS42) used to generate ~{CS} for each of the four 2016 2KB RAM chips using A_{11} and A_{12} addresses: 00 ... IC19 01 ... IC18 10 ... IC2 11 ... IC1 As I am using a single 62256 32KB RAM there is no need for this so I have ommitted it.
Unused Gates
